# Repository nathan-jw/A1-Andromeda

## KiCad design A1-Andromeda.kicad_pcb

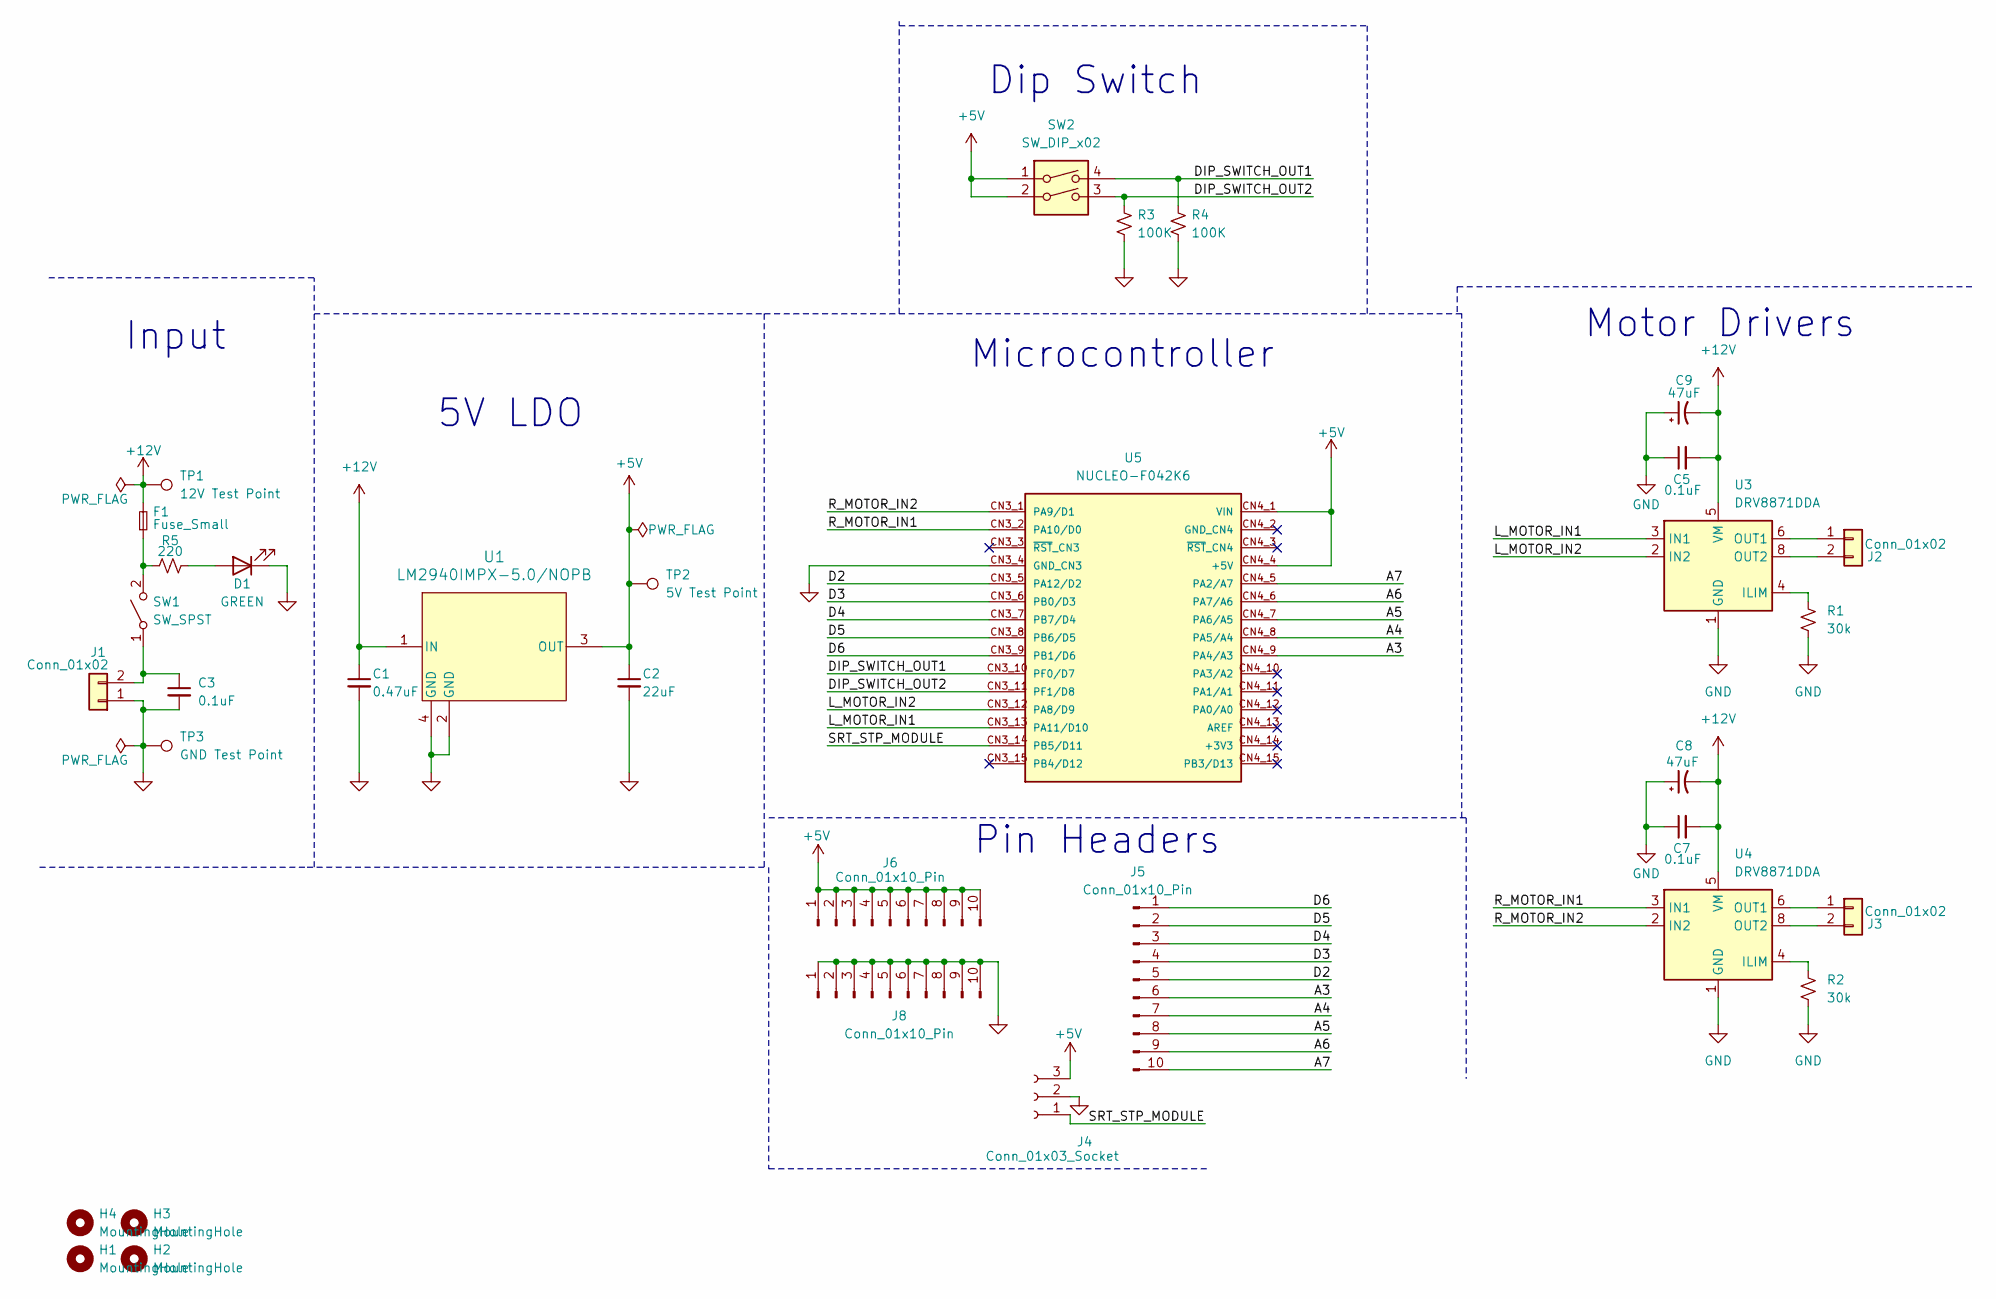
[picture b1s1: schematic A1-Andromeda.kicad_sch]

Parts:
C1: 0.47uF; C_1206_3216Metric
C2: 22uF; C_1206_3216Metric
C3, C5, C7: 0.1uF; C_1206_3216Metric
C8, C9: 47uF; CP_Radial_D5.0mm_P2.00mm
D1: GREEN; LED_1206_3216Metric
F1: Fuse_Small; Fuse_1206_3216Metric
H1, H2, H3, H4: MountingHole; MountingHole_2.2mm_M2
J1: Conn_01x02; AMASS_XT30U-M_1x02_P5.0mm_Vertical
J2, J3: Conn_01x02; JST_VH_B2P-VH_1x02_P3.96mm_Vertical
J4: Conn_01x03_Socket; PinSocket_1x03_P2.54mm_Vertical
J5, J6, J8: Conn_01x10_Pin; PinHeader_1x10_P2.54mm_Vertical
R1, R2: 30k; R_1206_3216Metric
R3, R4: 100K; C_1206_3216Metric
R5: 220; R_1206_3216Metric
SW1: SW_SPST; SW2_GF-123-0054_CWI
SW2: SW_DIP_x02; DS04-254-2-02BK-SMT_CUD
TP1: 12V Test Point; TestPoint_Keystone_5000-5004_Miniature
TP2: 5V Test Point; TestPoint_Keystone_5000-5004_Miniature
TP3: GND Test Point; TestPoint_Keystone_5000-5004_Miniature
U1: LM2940IMPX-5.0/NOPB; DCY0004A_N
U3, U4: DRV8871DDA; Texas_HTSOP-8-1EP_3.9x4.9mm_P1.27mm_EP2.95x4.9mm_Mask2.4x3.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
U5: NUCLEO-F042K6; MODULE_NUCLEO-F042K6; PARTREV 8

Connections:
+5V: C2.1, J4.3, J6.1, J6.2, J6.3, J6.4, J6.5, J6.6, J6.7, J6.8, J6.9, J6.10, SW2.1, SW2.2, TP2.1, U1.3 (OUT), U5.CN4_1 (VIN), U5.CN4_4 (+5V)
+12V: C1.1, C5.2, C7.2, C8.2, C9.2, F1.2, TP1.1, U1.1 (IN), U3.5 (VM), U4.5 (VM)
/A3: J5.6, U5.CN4_9 (PA4/A3)
/A4: J5.7, U5.CN4_8 (PA5/A4)
/A5: J5.8, U5.CN4_7 (PA6/A5)
/A6: J5.9, U5.CN4_6 (PA7/A6)
/A7: J5.10, U5.CN4_5 (PA2/A7)
/D2: J5.5, U5.CN3_5 (PA12/D2)
/D3: J5.4, U5.CN3_6 (PB0/D3)
/D4: J5.3, U5.CN3_7 (PB7/D4)
/D5: J5.2, U5.CN3_8 (PB6/D5)
/D6: J5.1, U5.CN3_9 (PB1/D6)
/DIP_SWITCH_OUT1: R4.1, SW2.4, U5.CN3_10 (PF0/D7)
/DIP_SWITCH_OUT2: R3.1, SW2.3, U5.CN3_11 (PF1/D8)
/L_MOTOR_IN1: U3.3 (IN1), U5.CN3_13 (PA11/D10)
/L_MOTOR_IN2: U3.2 (IN2), U5.CN3_12 (PA8/D9)
/R_MOTOR_IN1: U4.3 (IN1), U5.CN3_2 (PA10/D0)
/R_MOTOR_IN2: U4.2 (IN2), U5.CN3_1 (PA9/D1)
/SRT_STP_MODULE: J4.1, U5.CN3_14 (PB5/D11)
GND: C1.2, C2.2, C3.2, C5.1, C7.1, C8.1, C9.1, D1.1 (K), J1.1, J4.2, J8.1, J8.2, J8.3, J8.4, J8.5, J8.6, J8.7, J8.8, J8.9, J8.10, R1.2, R2.2, R3.2, R4.2, TP3.1, U1.2 (GND), U1.4 (GND), U3.1 (GND), U3.7 (GND), U3.9 (GND), U4.1 (GND), U4.7 (GND), U4.9 (GND), U5.CN3_4 (GND_CN3)
unnamed: D1.2 (A), R5.2
unnamed: C3.1, J1.2, SW1.1 (A)
unnamed: J2.1, U3.6 (OUT1)
unnamed: J2.2, U3.8 (OUT2)
unnamed: J3.1, U4.6 (OUT1)
unnamed: J3.2, U4.8 (OUT2)
unnamed: F1.1, R5.1, SW1.2 (B)
unnamed: R1.1, U3.4 (ILIM)
unnamed: R2.1, U4.4 (ILIM)

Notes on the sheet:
Dip Switch
Input
Microcontroller
5V LDO
Motor Drivers
Pin Headers

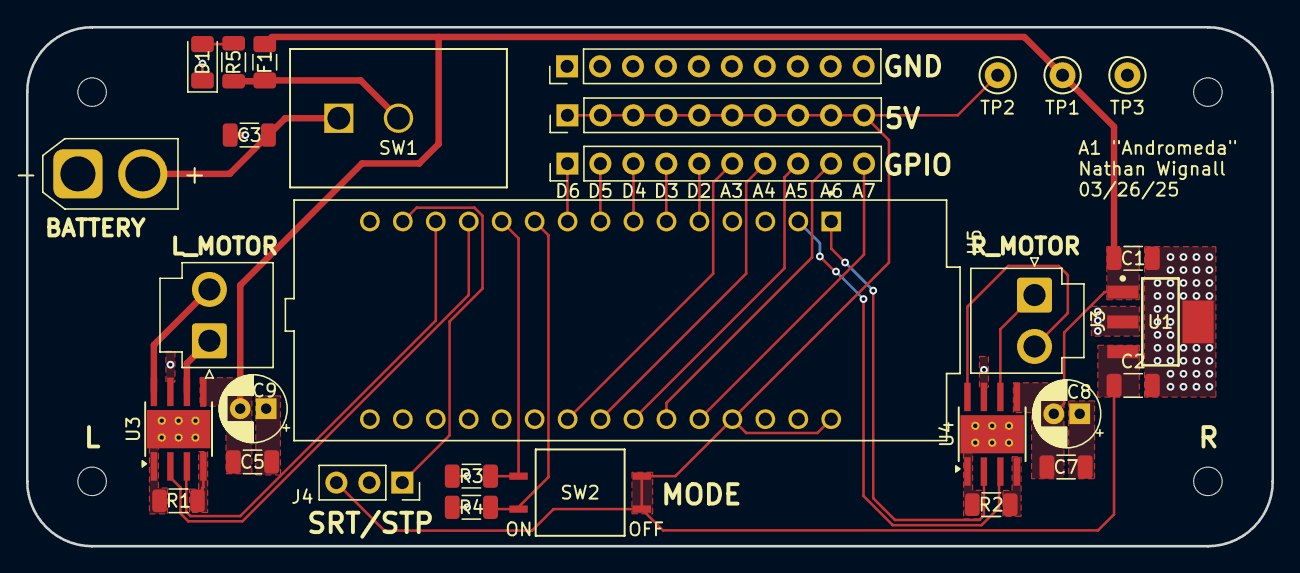
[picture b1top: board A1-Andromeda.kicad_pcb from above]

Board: 2 copper layers, 96.0 x 40.0 mm, 34 parts (0 on the bottom side), 29 nets.

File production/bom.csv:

Designator,Footprint,Quantity,Value,LCSC Part #
C1,1206,1,0.47uF,
C2,1206,1,22uF,
"C3, C5, C7",1206,3,0.1uF,
"C8, C9",CP_Radial_D5.0mm_P2.00mm,2,47uF,
D1,1206,1,GREEN,
F1,1206,1,Fuse_Small,
J1,AMASS_XT30U-M_1x02_P5.0mm_Vertical,1,Conn_01x02,
"J2, J3",JST_VH_B2P-VH_1x02_P3.96mm_Vertical,2,Conn_01x02,
J4,PinSocket_1x03_P2.54mm_Vertical,1,Conn_01x03_Socket,
"J5, J6, J8",PinHeader_1x10_P2.54mm_Vertical,3,Conn_01x10_Pin,
"R1, R2",1206,2,30k,
"R3, R4",1206,2,100K,
R5,1206,1,220,
SW1,SW2_GF-123-0054_CWI,1,SW_SPST,
SW2,DS04-254-2-02BK-SMT_CUD,1,SW_DIP_x02,
TP1,TestPoint_Keystone_5000-5004_Miniature,1,12V Test Point,
TP2,TestPoint_Keystone_5000-5004_Miniature,1,5V Test Point,
TP3,TestPoint_Keystone_5000-5004_Miniature,1,GND Test Point,
U1,DCY0004A_N,1,LM2940IMPX-5.0/NOPB,
U2,MODULE_NUCLEO-F042K6,1,NUCLEO-F042K6,
"U3, U4",Texas_HTSOP-8-1EP_3.9x4.9mm_P1.27mm_EP2.95x4.9mm_Mask2.4x3.1mm_ThermalVias,2,DRV8871DDA,

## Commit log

2025-02-25 remove bypass capacitors
2025-02-26 rotate GPIO pin array
2025-02-26 fix ground plane
2025-03-09 Create LICENSE
2025-03-13 redo PCB
2025-03-24 update silkscreen
2025-03-28 finish up
2025-04-29 fix VIN
2025-04-30 fix start/stop module pins
